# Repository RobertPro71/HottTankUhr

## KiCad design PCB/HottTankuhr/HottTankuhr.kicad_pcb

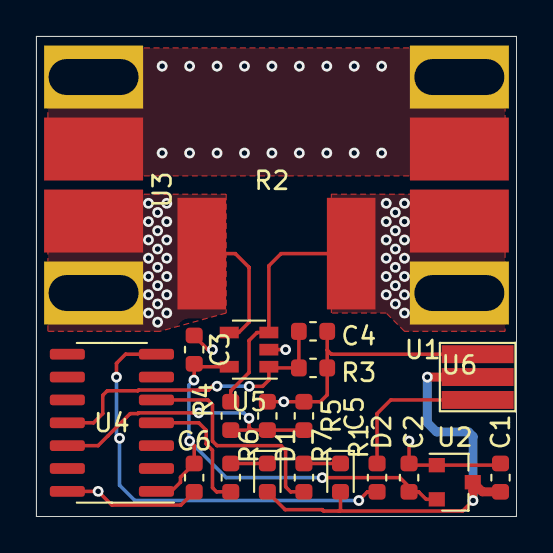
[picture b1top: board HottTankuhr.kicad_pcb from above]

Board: 2 copper layers, 26.7 x 26.7 mm, 21 parts (0 on the bottom side), 14 nets.

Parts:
C1, C2: 1µF; C_0603_1608Metric
C3, C6: 100n; C_0603_1608Metric
C4, C5: C; C_0603_1608Metric
D1, D2: LED; LED_0603_1608Metric
R1: 100R; R_0603_1608Metric
R2: R0002; BVS
R3, R4, R5, R6, R7: R; R_0603_1608Metric
U1: Servo_3x0.5; Servo_3x0.5_Lötpad
U2: MCP1700-3302E_SOT23; SOT-23
U3: MPX_male; MPX_female_lötpad
U4: ATtiny1614-SS; SOIC-14_3.9x8.7mm_P1.27mm
U5: INA138; SOT-23-5
U6: MPX_female; MPX_male_lötpad

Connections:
+3V3: C2.1, C3.2, C6.1, U2.2, U4.1, U5.5
+5V: C1.1, D1.2, D2.2, U1.2, U2.3
/+Batt: R2.2, R4.1, U5.3, U6.1, U6.2, U6.3
/+ESC: R2.1, U3.1, U3.2, U3.3, U5.4
/-Batt: U3.4, U3.5, U3.6, U6.4, U6.5, U6.6
/ADC_A: C4.1, R3.1, U4.11, U5.1
/ADC_V: C5.1, R4.2, R5.1, U4.12
/LED1: R6.1, U4.4
/LED2: R7.2, U4.5
/RxTx: R1.1, U4.7
/SIG: R1.2, U1.3
GND: C1.2, C2.2, C3.1, C4.2, C5.2, C6.2, R3.2, R5.2, U1.1, U2.1, U4.14, U5.2
unnamed: D1.1, R6.2
unnamed: D2.1, R7.1

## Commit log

2020-04-24 First add
2020-04-25 Add HootV4 Lib
2020-04-27 blinking led
2020-04-27 Change speed
2020-04-27 Init Uart
2020-05-01 dif uart setting
2020-05-01 Uart send running with interrupt
2020-05-02 ms Timer is running
2020-05-02 Sart build receive data
2020-05-03 Next step detect recv
2020-05-20 Uart works
2020-05-21 Begin adc
2020-06-04 First version PCB
2020-06-04 start ad converter
2020-06-11 remove EAM
2020-06-11 rewrite first byte
